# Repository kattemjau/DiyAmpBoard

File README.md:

# DiyAmpBoard
Diy amplifier breakout

Made in kicad

Made arround Tpa3116
http://www.farnell.com/datasheets/1813458.pdf

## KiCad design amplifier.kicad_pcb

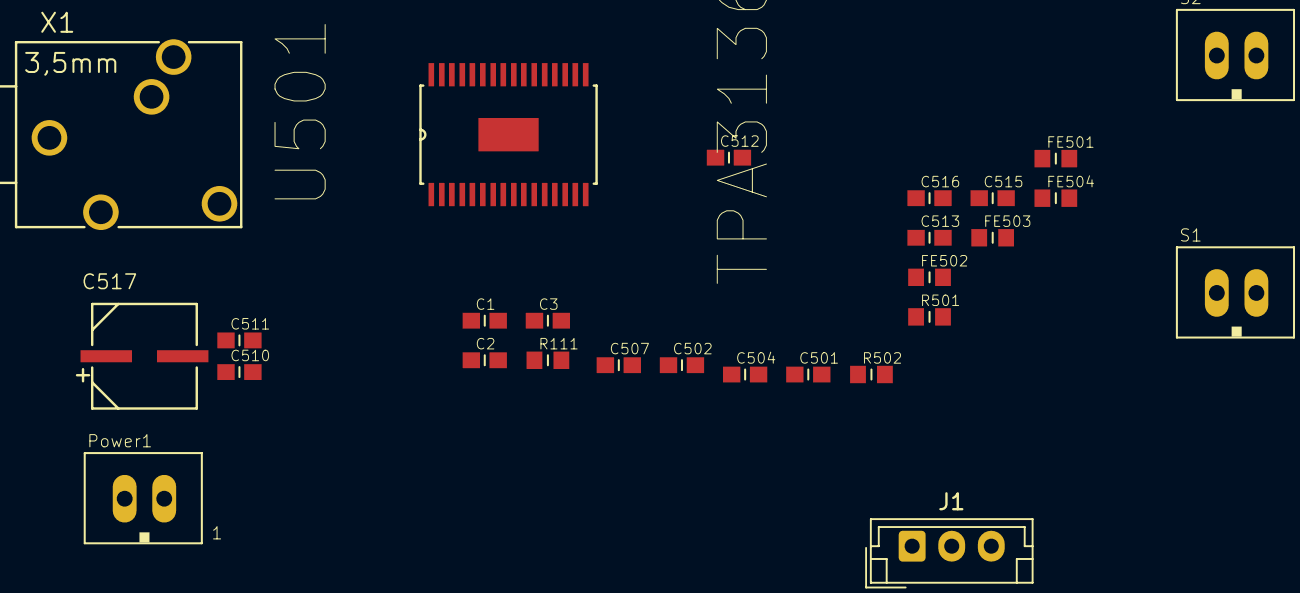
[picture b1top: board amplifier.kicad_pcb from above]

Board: 2 copper layers, 27 parts (0 on the bottom side), 21 nets, no tracks yet.

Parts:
C1, C501, C502, C504, C507: 1u; C0603
C2, C515: 1n; C0603
C3, C516: 100n; C0603
C510, C511, C512, C513: 220n; C0603
C517: 100u; CAP6.6X8
FE501, FE502, FE503, FE504: FERRITEBLM18SG700TN1; R0603
J1: Conn_01x03_Female; JST_EH_B03B-EH-A_1x03_P2.50mm_Vertical
Power1: CONNECTOR-2JST-XH-2; JST-XH-2
R111, R501: 100k; R0603
R502: 20k; R0603
S1, S2: CONNECTOR-2JST-XH-2; JST-XH-2
U501: TPA3136D2; SOP65P810X120-33N
X1: PG203J

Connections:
/12V: C2.1, C3.1, C515.1, C516.1, C517.1, Power1.P2, U501.17, U501.18, U501.19, U501.31, U501.32
/AUD_L: C501.1, X1.2
/AUD_R: C504.1, X1.5
GND: C1.2, C2.2, C3.2, C502.1, C515.2, C516.2, C517.2, J1.1, Power1.P1, R111.2, R502.2, U501.1, U501.9, U501.13, U501.14, U501.15, U501.22, U501.25, U501.28, U501.33, X1.1
unnamed: C1.1, J1.3, R501.2, U501.6, U501.7
unnamed: C501.2, U501.10
unnamed: C502.2, U501.5, U501.11
unnamed: C504.2, U501.4
unnamed: C510.1, U501.24
unnamed: C510.2, FE501.1, U501.23
unnamed: C511.1, U501.20
unnamed: C511.2, FE502.1, U501.21
unnamed: C512.1, U501.26
unnamed: C512.2, FE503.1, U501.27
unnamed: C513.1, U501.30
unnamed: C513.2, FE504.1, U501.29
unnamed: FE501.2, S1.P1
unnamed: FE502.2, S1.P2
unnamed: FE503.2, S2.P2
unnamed: FE504.2, S2.P1
unnamed: J1.2, R501.1, R502.1, U501.8

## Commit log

2019-02-27 first upload boi
    schematic 50% done
2019-02-27 added pdf of schematic
2019-03-03 updated ic
2019-03-03 added schematic
